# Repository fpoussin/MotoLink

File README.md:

View this project on [CADLAB.io](https://cadlab.io/node/808). 

MotoLink
===================

CAN Bus, K-Line interface for motorcycles, with a fuel/ignition mapper function.  

Primarily intended to communicate with Honda HRC, Generic OBD, or Yamaha YEC ECUs.  

This device will create a fuel map based on the various sensor inputs. You will then be able to alter the fuel using your prefered application. (HRC, TuneEcu, YEC, etc...)  
This replaces auto tune fuel systems like Bazzaz or Power commander, except you still have to enter the changes manually. (import/export functions are planned)  
Having a wideband exhaust sensor is mandatory. If your bike doesn't have one, you can use an innovate LC2.  

Includes some digital (RPM, Speed), analog (TPS, ECT, Wideband), serial (Wideband), as well as a knock sensor input interface for tuning.

### File tree:  
**├── Board**  *Eagle board files*  
**├── Code**  
**│   ├── App**  *Motolink's MCU code*  
**│   ├── Bootloader**  *STM32 Bootloader*  
**│   ├── ChibiOS-RT**  *ChibiOS/RT submodule*  
**│   ├── ChibiOS-Contrib**  *ChibiOS Community drivers submodule*  
**│   └── Common**  *Common files for bootloader and Motolink*  
**├── Drivers**  *Windows drivers installer*  
**├── GUI**  *Motolink's graphical user interface*  
**├── LICENSE**  *GPL Licence file*  
**└── README.md**  *This readme file*  

You will need to init and update the git submodules (QtUsb, ChibiOS-RT, ChibiOS-Contrib) to build the projects.

## Building
### GUI
* Make sure submodules are pulled
* You will need python 2/3 in the path (system path or Qt Creator project setting PATH variable)
* Go to the GUI folder
* Unzip res/oxygen.zip
* You need a binary file of the firmware, an empty one can be created for testing. (../code/app/build/motolink.bin)
* You need to install QtUsb (https://github.com/fpoussin/QtUsb)
* Open the project with Qt Creator
* Compile and launch

### App and Bootloader
* [You will need ARM's GCC toolchain](https://developer.arm.com/open-source/gnu-toolchain/gnu-rm/downloads)
* Make sure submodules are pulled
* Go the de code/app or code/bootloader folder
* For the app, you need to compile the DSP lib (just launch make in the dsp_lib folder)
* make
* For the bootloader, use your favorite stlink interface [or my QSTLink2 app](https://github.com/fpoussin/QStlink2)
* Once the bootloader is running, you can update the app through the GUI

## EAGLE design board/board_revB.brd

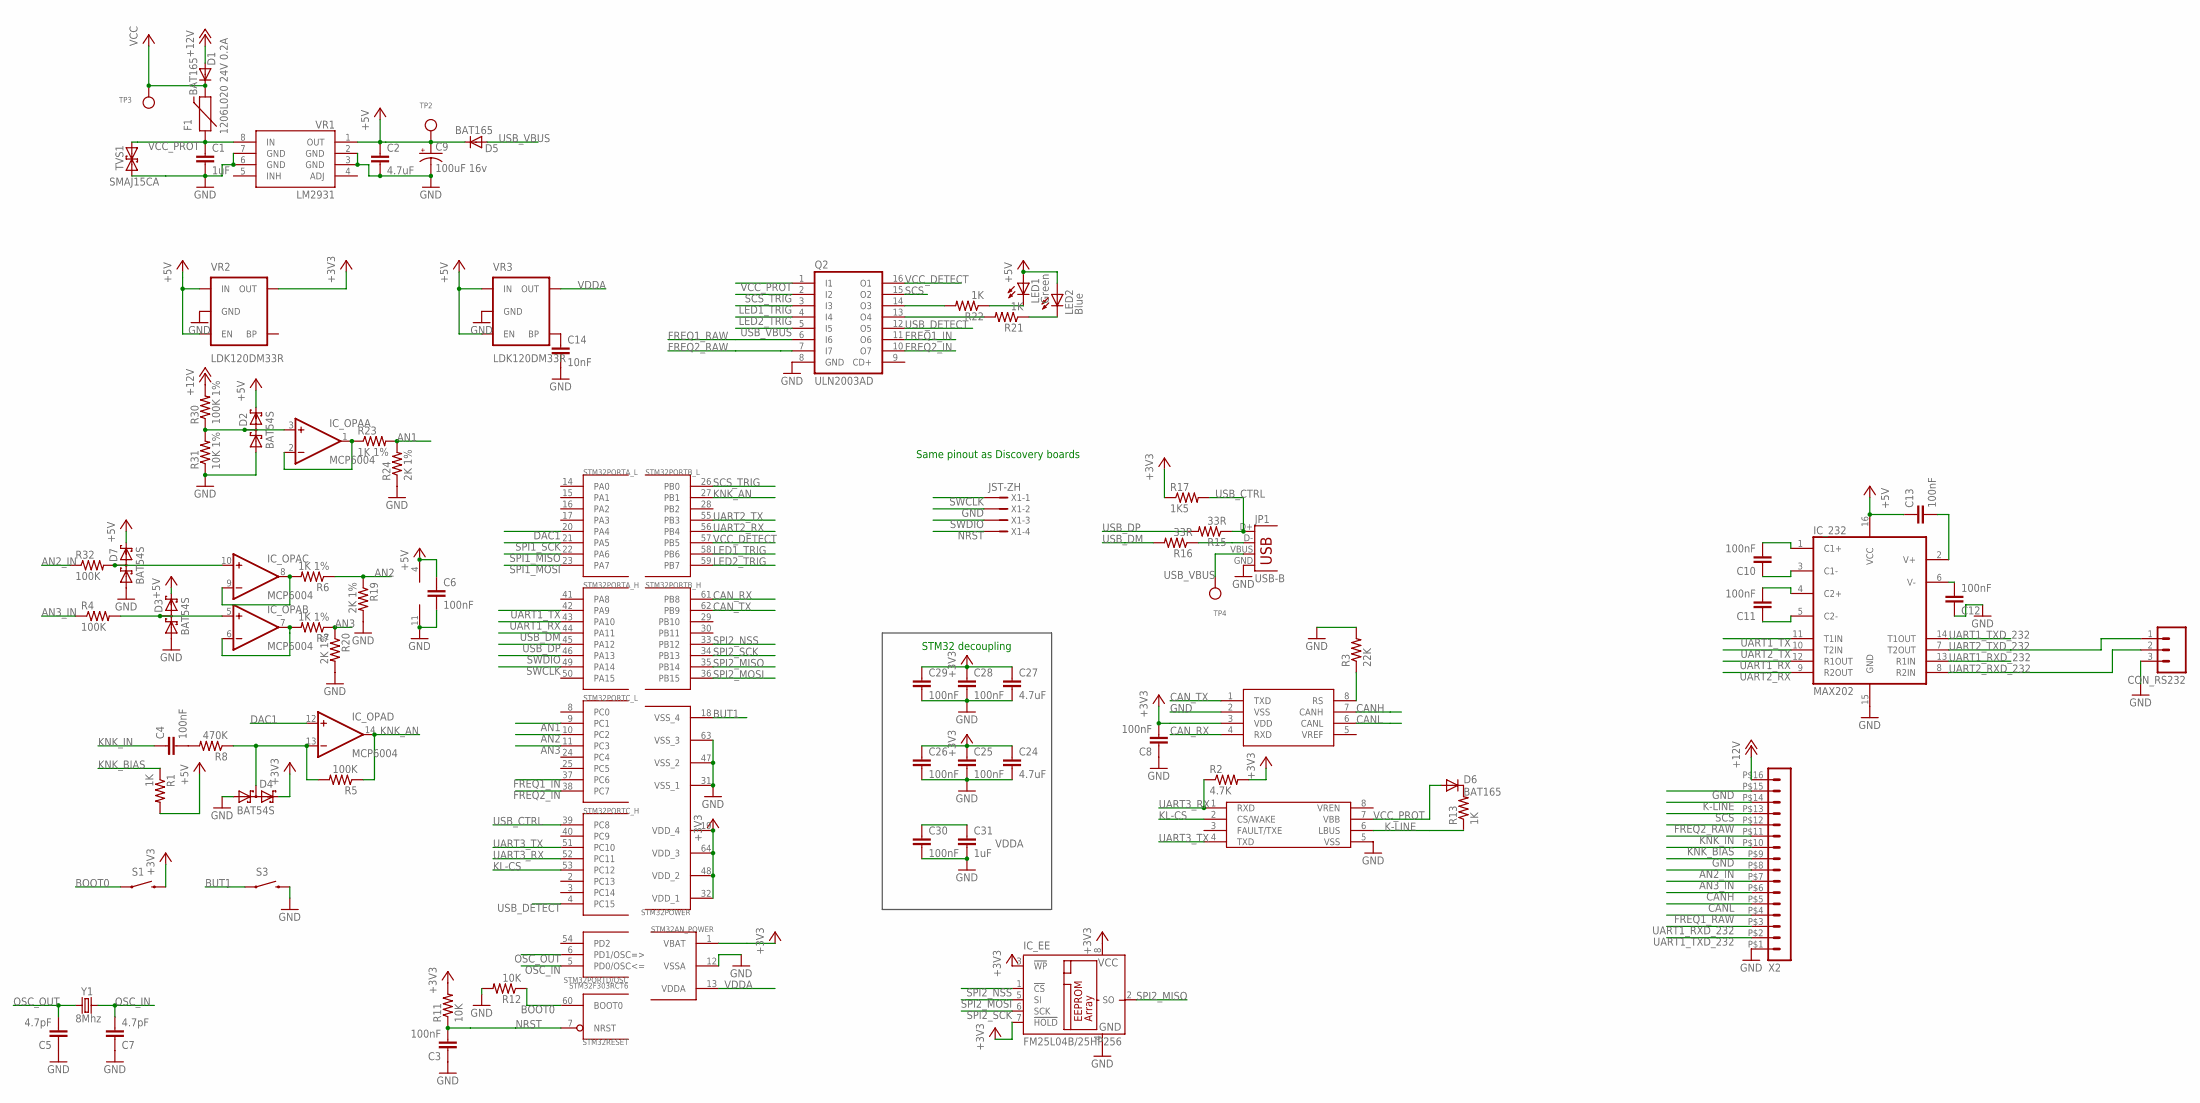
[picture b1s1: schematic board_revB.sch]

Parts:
C1, C31: 1uF; 0603-CAP
C2, C24, C27: 4.7uF; 0603-CAP
C3, C4, C6, C8, C10, C11, C12, C13, C25, C26, C28, C29, C30: 100nF; 0603-CAP
C5, C7: 4.7pF; 0603-CAP
C9: 100uF 16v; CPOL-RADIAL-10UF-25V
C14: 10nF; 0603-CAP
CON_RS232: M03LOCK; 1X03_LOCK
D1, D5, D6: BAT165; SOD-323
D2, D3, D4, D7: BAT54S; SOT23
F1: 1206L020 24V 0.2A; PTC-1206
IC_232: MAX202; TSSOP16
IC_CAN: MAX3051; SO08
IC_EE: FM25L04B/25HP256; SO-08
IC_KLINE: TJA1027; SO08
IC_OPA: MCP6004; TSSOP14
JP1: USB-B; USB-B-PTH
LED1: Green; LED3MM
LED2: Blue; LED3MM
Q2: ULN2003AD; SO16
R1, R13, R21, R22: 1K; 0603-RES
R2: 4.7K; 0603-RES
R3: 22K; 0603-RES
R4, R5, R32: 100K; 0603-RES
R6, R7, R23: 1K 1%; 0603-RES
R8: 470K; 0603-RES
R11, R12: 10K; 0603-RES
R15, R16: 33R; 0603-RES
R17: 1K5; 0603-RES
R19, R20, R24: 2K 1%; 0603-RES
R30: 100K 1%; 0603-RES
R31: 10K 1%; 0603-RES
S1: SWITCH-MOMENTARY-2SMD-4; TACTILE_SWITCH_TALL
S3: SWITCH-MOMENTARY-2SIDE_EZ; TACTILE-PTH-SIDEEZ
STM32: STM32F303RCT6; TQFP64
TP2, TP3, TP4: TESTPOINTROUND1MM; TESTPOINT_ROUND_1MM
TVS1: SMAJ15CA; SMA-DIODE
VR1: LM2931; SO08
VR2, VR3: LDK120DM33R; SOT23-5
X1: JST-ZH; S4B-ZR
X2: HEADER_POS16_43045-1600; 43045-1600
Y1: 8Mhz; HC49US

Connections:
+3V3: C8.2, C24.1, C25.1, C26.1, C27.1, C28.1, C29.1, D4.2 (C2), IC_CAN.3 (VDD), IC_EE.3 (!WP), IC_EE.7 (!HOLD), IC_EE.8 (VCC), R2.2, R11.2, R17.1, S1.B2 (2), STM32.1 (VBAT), STM32.19 (VDD_4), STM32.32 (VDD_1), STM32.48 (VDD_2), STM32.64 (VDD_3), VR2.5 (OUT)
+5V: C2.1, C6.1, C9.1 (+), C13.1, D2.2 (C2), D3.2 (C2), D5.1 (C), D7.2 (C2), IC_232.16 (VCC), IC_OPA.4 (V+), LED1.A, LED2.A, R1.2, TP2.P$1, VR1.1 (OUT), VR2.1 (IN), VR2.3 (EN), VR3.1 (IN), VR3.3 (EN)
+12V: D1.2 (A), R30.2, X2.P$16 (16)
AN1: R23.2, R24.2, STM32.9 (PC1)
AN1_N: IC_OPA.1 (OUT), IC_OPA.2 (-IN), R23.1
AN2: R6.1, R19.1, STM32.10 (PC2)
AN2_IN: R32.1, X2.P$8 (8)
AN2_N: IC_OPA.8 (OUT), IC_OPA.9 (-IN), R6.2
AN3: R7.1, R20.1, STM32.11 (PC3)
AN3_IN: R4.1, X2.P$7 (7)
AN3_N: IC_OPA.6 (-IN), IC_OPA.7 (OUT), R7.2
BOOT0: R12.1, S1.A2 (1), STM32.60 (BOOT0)
BUT1: S3.1, STM32.18 (VSS_4)
CANH: IC_CAN.7 (CANH), X2.P$6 (6)
CANL: IC_CAN.6 (CANL), X2.P$5 (5)
CAN_RX: IC_CAN.4 (RXD), STM32.61 (PB8)
CAN_TX: IC_CAN.1 (TXD), STM32.62 (PB9)
DAC1: IC_OPA.12 (+IN), STM32.20 (PA4)
FREQ1_IN: Q2.11 (O6), STM32.37 (PC6)
FREQ1_RAW: Q2.6 (I6), X2.P$4 (4)
FREQ2_IN: Q2.10 (O7), STM32.38 (PC7)
FREQ2_RAW: Q2.7 (I7), X2.P$12 (12)
GND: C1.2, C2.2, C3.1, C5.1, C6.2, C7.1, C8.1, C9.2 (-), C12.1, C14.2, C24.2, C25.2, C26.2, C27.2, C28.2, C29.2, C30.2, C31.2, CON_RS232.3, D2.1 (A1), D3.1 (A1), D4.1 (A1), D7.1 (A1), IC_232.15 (GND), IC_CAN.2 (VSS), IC_EE.4 (GND), IC_KLINE.5 (VSS), IC_OPA.11 (V-), JP1.GND, Q2.8 (GND), R3.2, R12.2, R19.2, R20.2, R24.1, R31.1, S3.2, STM32.12 (VSSA), STM32.31 (VSS_1), STM32.47 (VSS_2), STM32.63 (VSS_3), TVS1.A (1), VR1.2 (GND), VR1.3 (GND), VR1.6 (GND), VR1.7 (GND), VR2.2 (GND), VR3.2 (GND), X1.2, X2.P$1 (1), X2.P$9 (9), X2.P$15 (15)
K-LINE: IC_KLINE.6 (LBUS), R13.1, X2.P$14 (14)
KL-CS: IC_KLINE.2 (CS/WAKE), STM32.53 (PC12)
KNK_AN: IC_OPA.14 (OUT), R5.1, STM32.27 (PB1)
KNK_BIAS: R1.1, X2.P$10 (10)
KNK_IN: C4.1, X2.P$11 (11)
LED1_TRIG: Q2.3 (I3), STM32.58 (PB6)
LED2_TRIG: Q2.4 (I4), STM32.59 (PB7)
unnamed: D4.3 (C1A2), IC_OPA.13 (-IN), R5.2, R8.1
unnamed: D3.3 (C1A2), IC_OPA.5 (+IN), R4.2
unnamed: C4.2, R8.2
unnamed: IC_CAN.8 (RS), R3.1
unnamed: C14.1, VR3.4 (BP)
unnamed: LED2.K (C), R21.1
unnamed: Q2.13 (O4), R21.2
unnamed: D6.1 (C), R13.2
unnamed: Q2.14 (O3), R22.2
unnamed: JP1.D-, R16.1
unnamed: LED1.K (C), R22.1
unnamed: C11.2, IC_232.4 (C2+)
unnamed: C11.1, IC_232.5 (C2-)
unnamed: C10.1, IC_232.3 (C1-)
unnamed: D2.3 (C1A2), IC_OPA.3 (+IN), R30.1, R31.2
unnamed: D7.3 (C1A2), IC_OPA.10 (+IN), R32.2
unnamed: C10.2, IC_232.1 (C1+)
unnamed: C12.2, IC_232.6 (V-)
unnamed: C13.2, IC_232.2 (V+)
NRST: C3.2, R11.1, STM32.7 (NRST), X1.4
OSC_IN: C7.2, STM32.5 (PD0/OSC<=), Y1.2
OSC_OUT: C5.2, STM32.6 (PD1/OSC=>), Y1.1
SCS: Q2.15 (O2), X2.P$13 (13)
SCS_TRIG: Q2.2 (I2), STM32.26 (PB0)
SPI1_MISO: STM32.22 (PA6)
SPI1_MOSI: STM32.23 (PA7)
SPI1_SCK: STM32.21 (PA5)
SPI2_MISO: IC_EE.2 (SO), STM32.35 (PB14)
SPI2_MOSI: IC_EE.5 (SI), STM32.36 (PB15)
SPI2_NSS: IC_EE.1 (!CS), STM32.33 (PB12)
SPI2_SCK: IC_EE.6 (SCK), STM32.34 (PB13)
SWCLK: STM32.49 (PA14), X1.1
SWDIO: STM32.46 (PA13), X1.3
UART1_RX: IC_232.12 (R1OUT), STM32.43 (PA10)
UART1_RXD_232: IC_232.13 (R1IN), X2.P$3 (3)
UART1_TX: IC_232.11 (T1IN), STM32.42 (PA9)
UART1_TXD_232: IC_232.14 (T1OUT), X2.P$2 (2)
UART2_RX: IC_232.9 (R2OUT), STM32.56 (PB4)
UART2_RXD_232: CON_RS232.2, IC_232.8 (R2IN)
UART2_TX: IC_232.10 (T2IN), STM32.55 (PB3)
UART2_TXD_232: CON_RS232.1, IC_232.7 (T2OUT)
UART3_RX: IC_KLINE.1 (RXD), R2.1, STM32.52 (PC11)
UART3_TX: IC_KLINE.4 (TXD), STM32.51 (PC10)
USB_CTRL: JP1.D+, R15.1, R17.2, STM32.39 (PC8)
USB_DETECT: Q2.12 (O5), STM32.4 (PC15)
USB_DM: R16.2, STM32.44 (PA11)
USB_DP: R15.2, STM32.45 (PA12)
USB_VBUS: D5.2 (A), JP1.VBUS, Q2.5 (I5), TP4.P$1
VCC: D1.1 (C), F1.2, TP3.P$1
VCC_DETECT: Q2.16 (O1), STM32.57 (PB5)
VCC_PROT: C1.1, D6.2 (A), F1.1, IC_KLINE.7 (VBB), Q2.1 (I1), TVS1.C (2), VR1.8 (IN)
VDDA: C30.1, C31.1, STM32.13 (VDDA), VR3.5 (OUT)

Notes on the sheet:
STM32 decoupling
Same pinout as Discovery boards

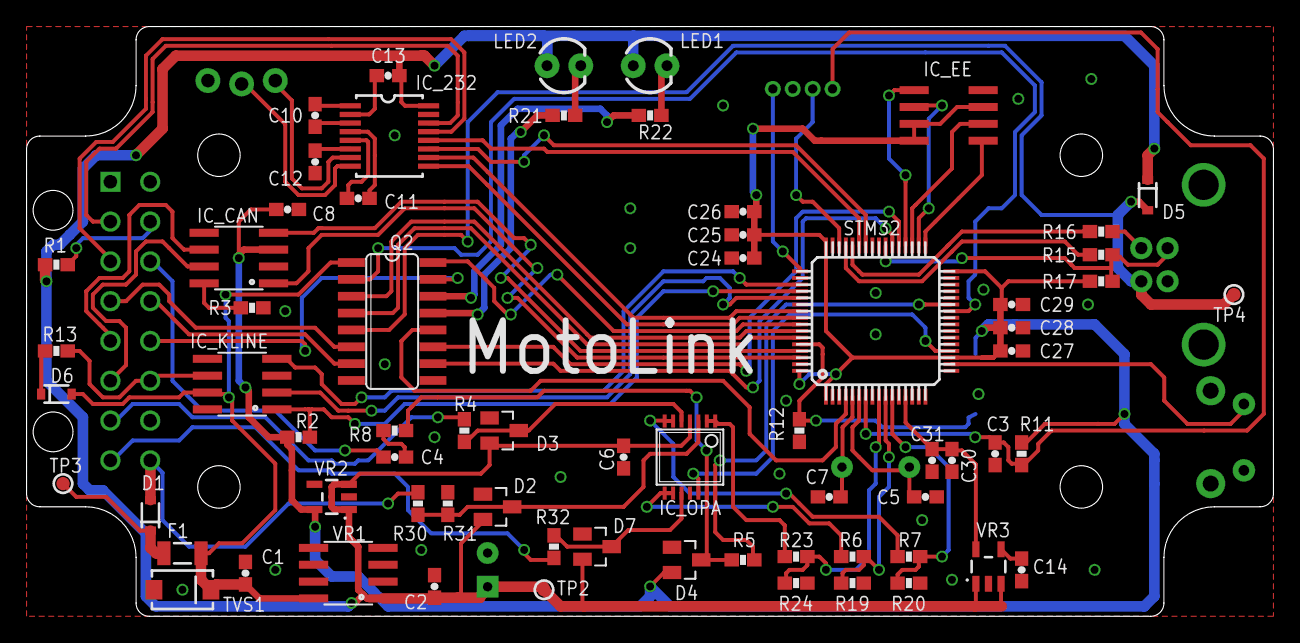
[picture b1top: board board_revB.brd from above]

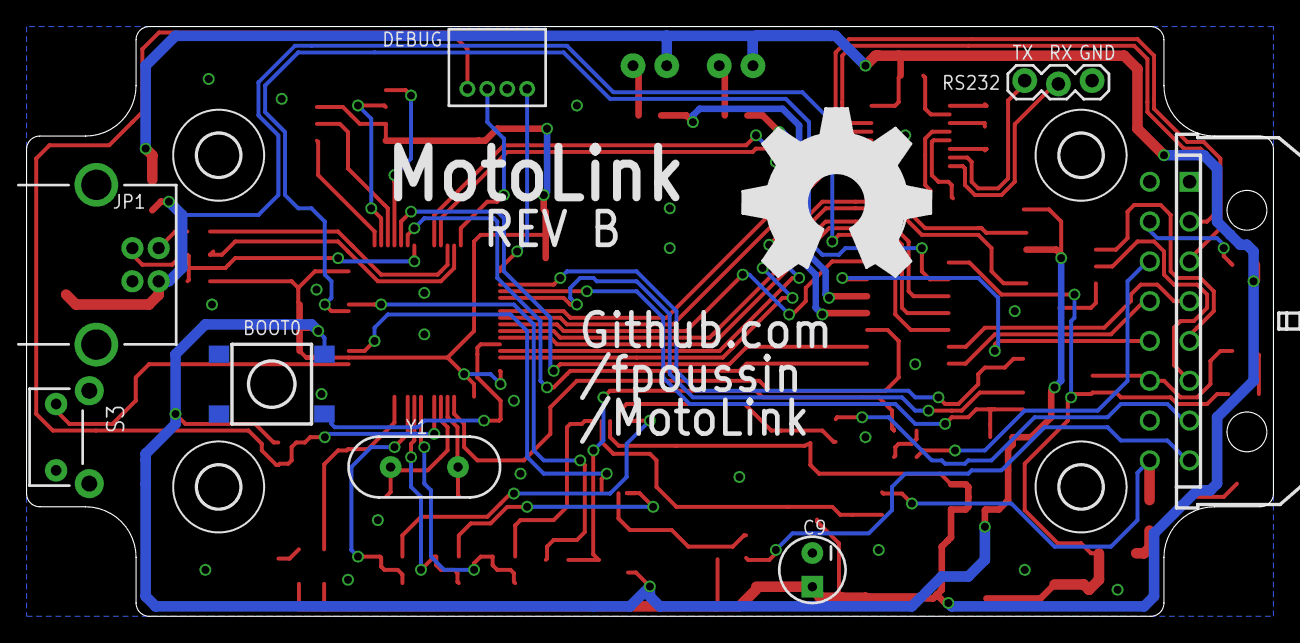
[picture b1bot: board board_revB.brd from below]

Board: 2 copper layers, 94.0 x 44.5 mm, 81 parts (13 on the bottom side), 79 nets.

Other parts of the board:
U$2, U$3, U$4, U$5: 3,2
U$6: OSHW_FILLX500_NOTEXT

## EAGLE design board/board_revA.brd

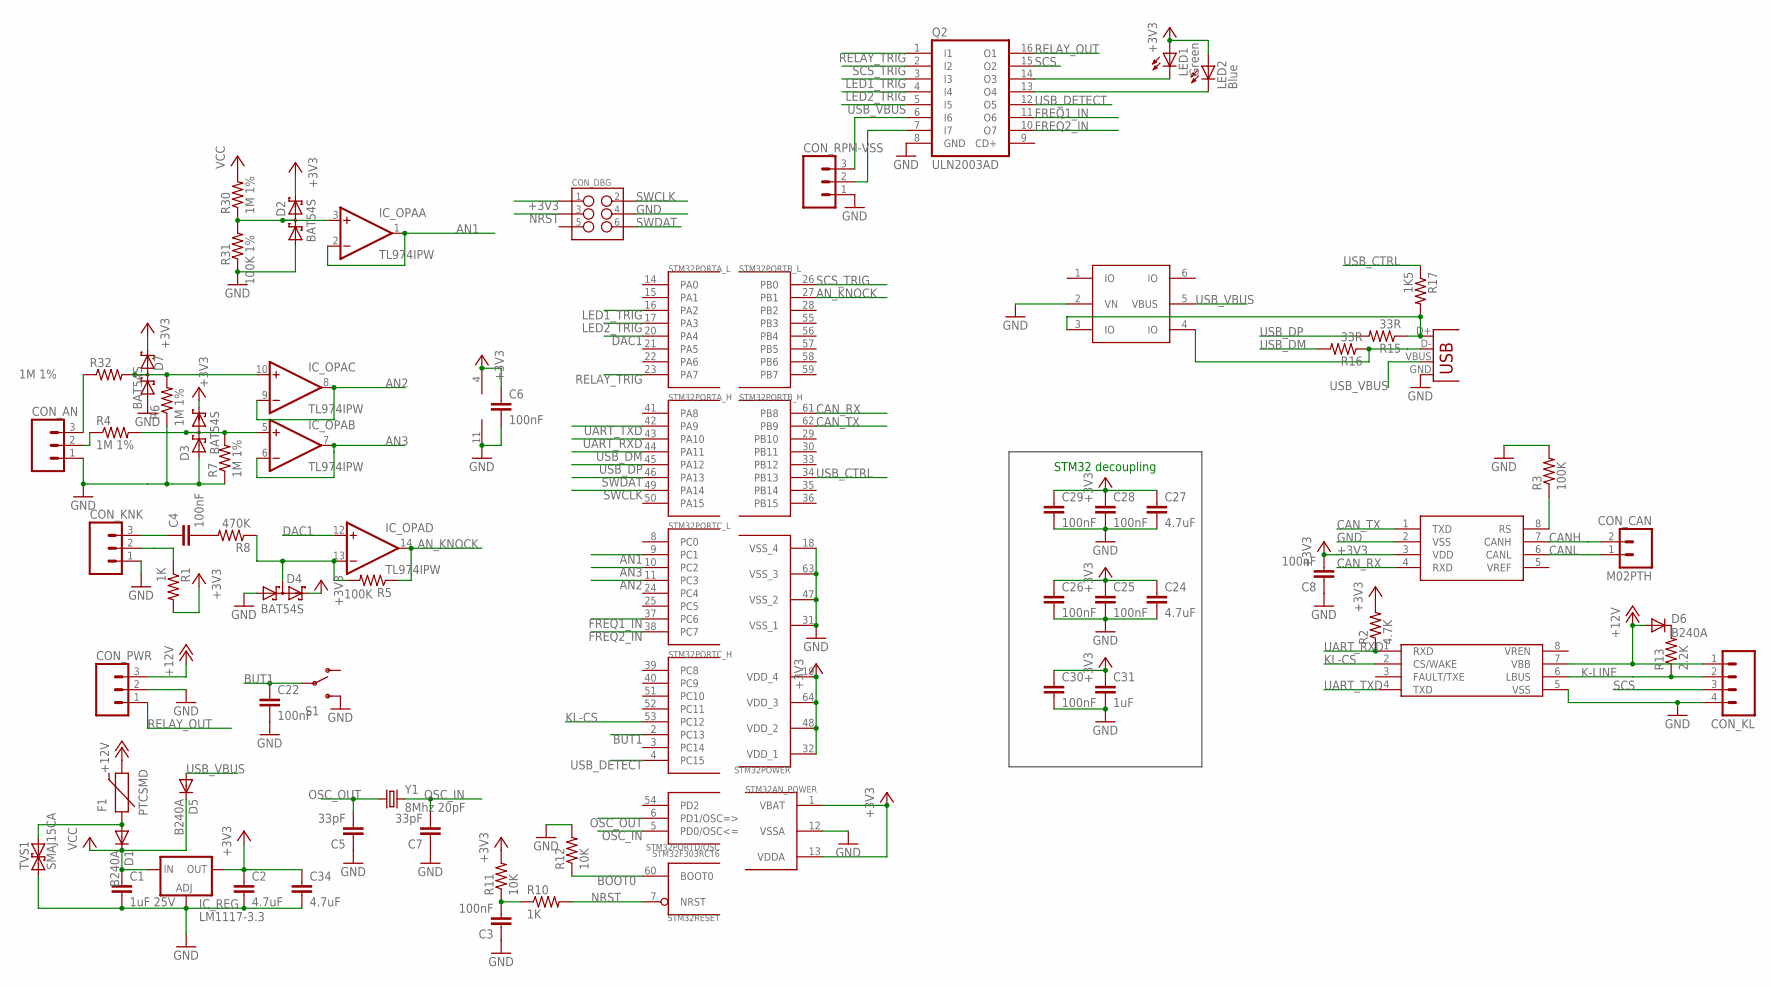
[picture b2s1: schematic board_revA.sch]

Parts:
C1: 1uF 25V; 0603-CAP
C2, C24, C27, C34: 4.7uF; 0603-CAP
C3, C4, C6, C8, C22, C25, C26, C28, C29, C30: 100nF; 0603-CAP
C5, C7: 33pF; 0603-CAP
C31: 1uF; 0603-CAP
CON_AN: M03PTH; 1X03
CON_CAN: M02PTH; 1X02
CON_DBG: M03X22X3_SILK_SM; 2X3
CON_KL: M04PTH; 1X04
CON_KNK: M03PTH; 1X03
CON_PWR: M03PTH; 1X03
CON_RPM-VSS: M03PTH; 1X03
CON_USB: USBSMD; USB-MINIB
D1, D5, D6: B240A; SMA-DIODE
D2, D3, D4, D7: BAT54S; SOT23
F1: PTCSMD; PTC-1206
IC_CAN: MAX3051; SO08
IC_KLINE: MCP2004; SO08
IC_OPA: TL974IPW; TSSOP14
IC_REG: LM1117-3.3; DPACK
LED1: Green; LED3MM
LED2: Blue; LED3MM
Q2: ULN2003AD; SO16
R1, R10: 1K; 0603-RES
R2: 4.7K; 0603-RES
R3, R5: 100K; 0603-RES
R4, R6, R7, R30, R32: 1M 1%; 0603-RES
R8: 470K; 0603-RES
R11, R12: 10K; 0603-RES
R13: 2.2K; 0603-RES
R15, R16: 33R; 0603-RES
R17: 1K5; 0603-RES
R31: 100K 1%; 0603-RES
S1: SWITCH-SPDTPTH; SWITCH-SPDT
STM32: STM32F303RCT6; TQFP64
TVS1: SMAJ15CA; SMA-DIODE
TVS2: NUP4201MR6; SOT23-6
Y1: 8Mhz 20pF; HC49US

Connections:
+3V3: C2.1, C6.1, C8.2, C24.1, C25.1, C26.1, C27.1, C28.1, C29.1, C30.1, C31.1, C34.1, CON_DBG.1, D2.2 (C2), D3.2 (C2), D4.2 (C2), D7.2 (C2), IC_CAN.3 (VDD), IC_OPA.4 (V+), IC_REG.4 (OUT), LED1.A, LED2.A, R1.2, R2.2, R11.2, STM32.1 (VBAT), STM32.13 (VDDA), STM32.19 (VDD_4), STM32.32 (VDD_1), STM32.48 (VDD_2), STM32.64 (VDD_3)
+12V: CON_KL.1, CON_PWR.3, D6.A, F1.2, IC_KLINE.7 (VBB)
AN1: IC_OPA.1 (OUT), IC_OPA.2 (-IN), STM32.9 (PC1)
AN2: IC_OPA.8 (OUT), IC_OPA.9 (-IN), STM32.11 (PC3)
AN3: IC_OPA.6 (-IN), IC_OPA.7 (OUT), STM32.10 (PC2)
AN_KNOCK: IC_OPA.14 (OUT), R5.1, STM32.27 (PB1)
BOOT0: R12.1, STM32.60 (BOOT0)
BUT1: C22.1, S1.2, STM32.2 (PC13)
CANH: CON_CAN.2, IC_CAN.7 (CANH)
CANL: CON_CAN.1, IC_CAN.6 (CANL)
CAN_RX: IC_CAN.4 (RXD), STM32.61 (PB8)
CAN_TX: IC_CAN.1 (TXD), STM32.62 (PB9)
DAC1: IC_OPA.12 (+IN), STM32.20 (PA4)
FREQ1_IN: Q2.11 (O6), STM32.37 (PC6)
FREQ2_IN: Q2.10 (O7), STM32.38 (PC7)
GND: C1.2, C2.2, C3.1, C5.1, C6.2, C7.1, C8.1, C22.2, C24.2, C25.2, C26.2, C27.2, C28.2, C29.2, C30.2, C31.2, C34.2, CON_AN.1, CON_DBG.4, CON_KL.4, CON_KNK.1, CON_PWR.2, CON_RPM-VSS.1, CON_USB.GND, D2.1 (A1), D3.1 (A1), D4.1 (A1), D7.1 (A1), IC_CAN.2 (VSS), IC_KLINE.5 (VSS), IC_OPA.11 (V-), IC_REG.1 (ADJ), Q2.8 (GND), R3.2, R6.1, R7.1, R12.2, R31.1, S1.3 (S), STM32.12 (VSSA), STM32.18 (VSS_4), STM32.31 (VSS_1), STM32.47 (VSS_2), STM32.63 (VSS_3), TVS1.A (1), TVS2.2 (VN)
K-LINE: CON_KL.2, IC_KLINE.6 (LBUS), R13.1
KL-CS: IC_KLINE.2 (CS/WAKE), STM32.53 (PC12)
LED1_TRIG: Q2.3 (I3), STM32.16 (PA2)
LED2_TRIG: Q2.4 (I4), STM32.17 (PA3)
unnamed: CON_KNK.2, R1.1
unnamed: CON_AN.3, R32.1
unnamed: CON_AN.2, R4.1
unnamed: C4.1, CON_KNK.3
unnamed: D3.3 (C1A2), IC_OPA.5 (+IN), R4.2, R7.2
unnamed: C4.2, R8.2
unnamed: CON_USB.D+, R15.1, R17.2, TVS2.3 (IO)
unnamed: IC_CAN.8 (RS), R3.1
unnamed: D1.A, F1.1, TVS1.C (2)
unnamed: LED1.K (C), Q2.14 (O3)
unnamed: LED2.K (C), Q2.13 (O4)
unnamed: D4.3 (C1A2), IC_OPA.13 (-IN), R5.2, R8.1
unnamed: D6.C, R13.2
unnamed: CON_RPM-VSS.3, Q2.6 (I6)
unnamed: CON_USB.D-, R16.1, TVS2.4 (IO)
unnamed: C3.2, R10.1, R11.1
unnamed: CON_RPM-VSS.2, Q2.7 (I7)
unnamed: D2.3 (C1A2), IC_OPA.3 (+IN), R30.1, R31.2
unnamed: D7.3 (C1A2), IC_OPA.10 (+IN), R6.2, R32.2
NRST: CON_DBG.3, R10.2, STM32.7 (NRST)
OSC_IN: C7.2, STM32.5 (PD0/OSC<=), Y1.2
OSC_OUT: C5.2, STM32.6 (PD1/OSC=>), Y1.1
RELAY_OUT: CON_PWR.1, Q2.16 (O1)
RELAY_TRIG: Q2.1 (I1), STM32.23 (PA7)
SCS: CON_KL.3, Q2.15 (O2)
SCS_TRIG: Q2.2 (I2), STM32.26 (PB0)
SWCLK: CON_DBG.2, STM32.49 (PA14)
SWDAT: CON_DBG.6, STM32.46 (PA13)
UART_RXD: IC_KLINE.1 (RXD), R2.1, STM32.43 (PA10)
UART_TXD: IC_KLINE.4 (TXD), STM32.42 (PA9)
USB_CTRL: R17.1, STM32.34 (PB13)
USB_DETECT: Q2.12 (O5), STM32.4 (PC15)
USB_DM: R16.2, STM32.44 (PA11)
USB_DP: R15.2, STM32.45 (PA12)
USB_VBUS: CON_USB.VBUS, D5.A, Q2.5 (I5), TVS2.5 (VBUS)
VCC: C1.1, D1.C, D5.C, IC_REG.3 (IN), R30.2

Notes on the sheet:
STM32 decoupling

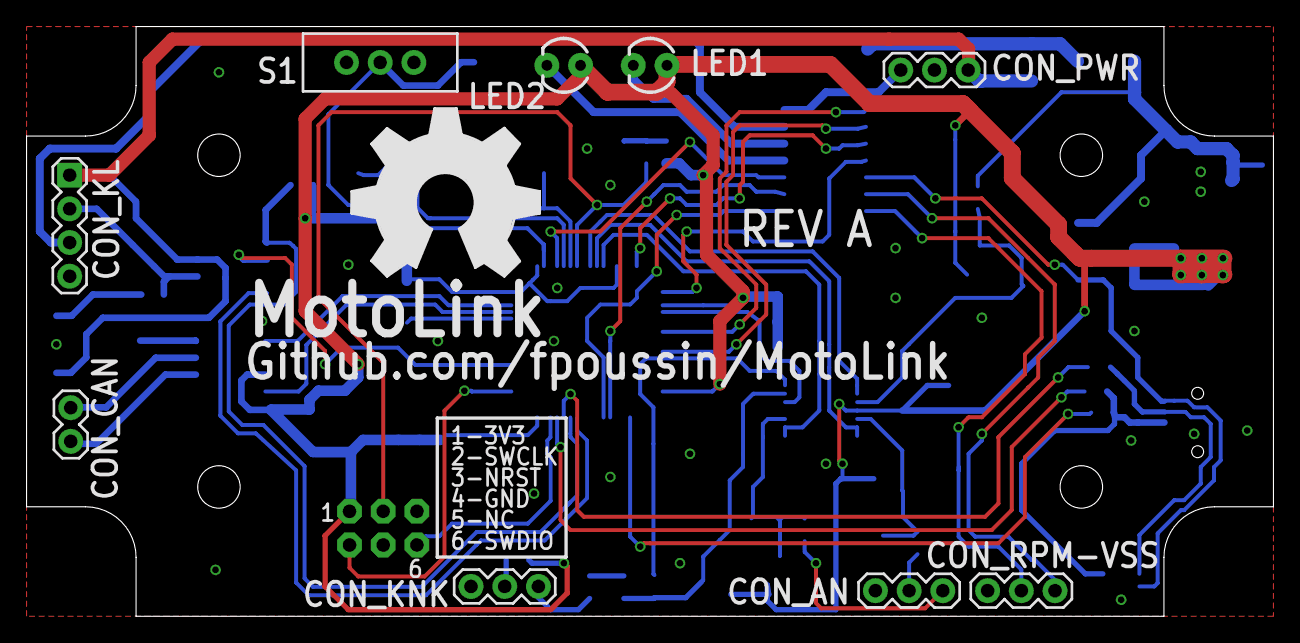
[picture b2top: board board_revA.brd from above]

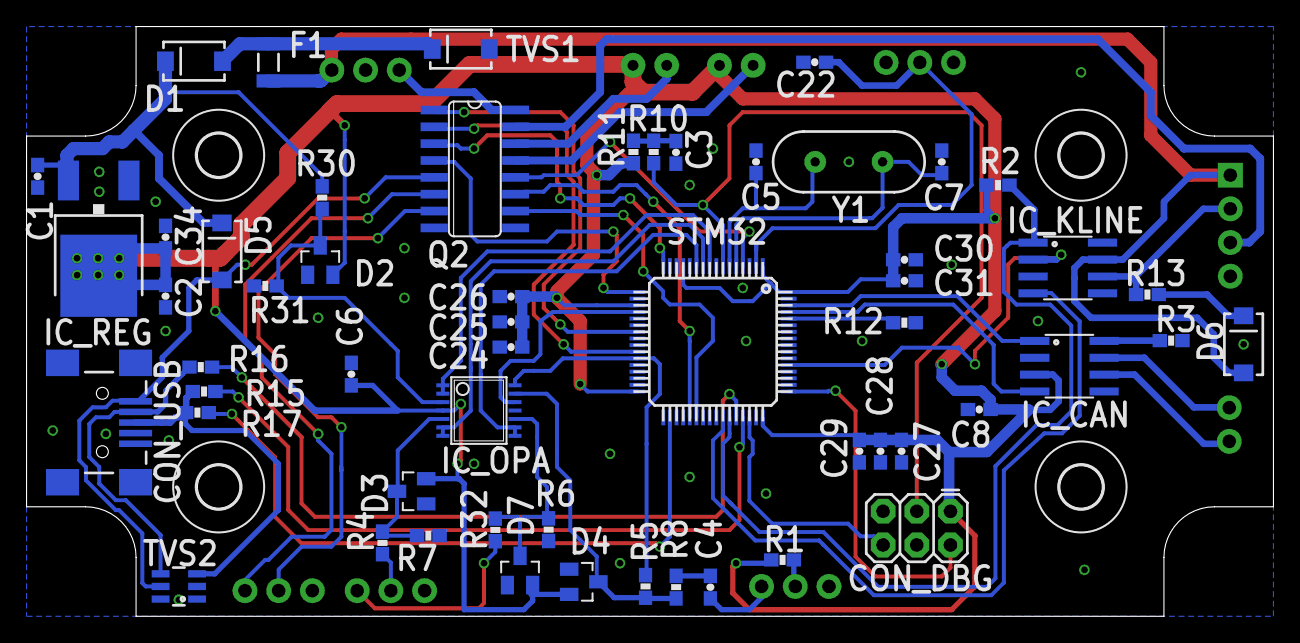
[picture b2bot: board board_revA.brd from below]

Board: 2 copper layers, 94.0 x 44.5 mm, 69 parts (59 on the bottom side), 56 nets.

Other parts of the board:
U$2, U$3, U$4, U$5: 3,2
U$6: OSHW_FILLX500_NOTEXT

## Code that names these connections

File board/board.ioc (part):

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Mcu.Name=STM32F303R(B-C)Tx
Mcu.Package=LQFP64
Mcu.UserName=STM32F303R(B-C)Tx
PA10.GPIOParameters=GPIO_Speed,GPIO_PuPd,GPIO_OType,GPIO_Mode
PA10.GPIO_Mode=GPIO_MODE_AF_PP
PA10.GPIO_OType=N/A
PA10.GPIO_PuPd=GPIO_PULLUP
PA10.GPIO_Speed=GPIO_SPEED_FREQ_MEDIUM
PA10.Mode=Asynchronous
PA10.Signal=USART1_RX
PA11.Mode=Device
PA11.Signal=USB_DM
PA12.Mode=Device
PA12.Signal=USB_DP
PA13.Mode=Serial_Wire
PA13.Signal=SYS_JTMS-SWDIO
PA14.Mode=Serial_Wire
PA14.Signal=SYS_JTCK-SWCLK
PA4.GPIOParameters=GPIO_PuPd,GPIO_Label,GPIO_Mode
PA4.GPIO_Label=KNOCK_OFFSET
PA4.GPIO_Mode=GPIO_MODE_ANALOG
PA4.GPIO_PuPd=GPIO_NOPULL
PA4.Signal=COMP_DAC1_group
PA9.GPIOParameters=GPIO_Speed,GPIO_PuPd,GPIO_OType,GPIO_Mode
PA9.GPIO_Mode=GPIO_MODE_AF_PP
PA9.GPIO_OType=N/A
PA9.GPIO_PuPd=GPIO_PULLUP
PA9.GPIO_Speed=GPIO_SPEED_FREQ_MEDIUM
PA9.Mode=Asynchronous
PA9.Signal=USART1_TX
PB0.GPIOParameters=GPIO_Speed,GPIO_PuPd,GPIO_Label,GPIO_ModeDefaultOutputPP
PB0.GPIO_Label=SCS_TRIG
PB0.GPIO_ModeDefaultOutputPP=GPIO_MODE_OUTPUT_PP
PB0.GPIO_PuPd=GPIO_NOPULL
PB0.GPIO_Speed=GPIO_SPEED_FREQ_LOW
PB0.Signal=GPIO_Output
PB1.GPIOParameters=GPIO_PuPd,GPIO_Label,GPIO_Mode
PB1.GPIO_Label=KNK_AN
PB1.GPIO_Mode=GPIO_MODE_ANALOG
PB1.GPIO_PuPd=GPIO_NOPULL
PB1.Mode=IN1-Single-Ended
PB1.Signal=ADC3_IN1
PB12.Mode=NSS_Signal_Hard_Input
PB12.Signal=SPI2_NSS
PB13.Mode=Full_Duplex_Master
PB13.Signal=SPI2_SCK
PB14.Mode=Full_Duplex_Master
PB14.Signal=SPI2_MISO
PB15.Mode=Full_Duplex_Master
PB15.Signal=SPI2_MOSI
PB3.GPIOParameters=GPIO_Speed
PB3.GPIO_Speed=GPIO_SPEED_FREQ_MEDIUM
PB3.Mode=Asynchronous
PB3.Signal=USART2_TX
PB4.GPIOParameters=GPIO_Speed
PB4.GPIO_Speed=GPIO_SPEED_FREQ_MEDIUM
PB4.Mode=Asynchronous
PB4.Signal=USART2_RX
PB5.GPIOParameters=GPIO_PuPd,GPIO_Label
PB5.GPIO_Label=VCC_DETECT
PB5.GPIO_PuPd=GPIO_PULLUP
PB5.Signal=GPIO_Input
PB6.GPIOParameters=GPIO_ModeDefaultPP,GPIO_Speed,GPIO_FM6,GPIO_PuPd,GPIO_Label
PB6.GPIO_FM6=__NULL
PB6.GPIO_Label=LED1
PB6.GPIO_ModeDefaultPP=GPIO_MODE_AF_PP
PB6.GPIO_PuPd=GPIO_NOPULL
PB6.GPIO_Speed=GPIO_SPEED_FREQ_LOW
PB6.Signal=S_TIM4_CH1
PB7.GPIOParameters=GPIO_ModeDefaultPP,GPIO_Speed,GPIO_PuPd,GPIO_Label,GPIO_FM7
PB7.GPIO_FM7=__NULL
PB7.GPIO_Label=LED2
PB7.GPIO_ModeDefaultPP=GPIO_MODE_AF_PP
PB7.GPIO_PuPd=GPIO_NOPULL
PB7.GPIO_Speed=GPIO_SPEED_FREQ_LOW
PB7.Signal=S_TIM4_CH2
PB8.GPIOParameters=GPIO_Speed,GPIO_PuPd,GPIO_FM8,GPIO_Mode
PB8.GPIO_FM8=__NULL
PB8.GPIO_Mode=GPIO_MODE_AF_PP
PB8.GPIO_PuPd=GPIO_NOPULL
PB8.GPIO_Speed=GPIO_SPEED_FREQ_MEDIUM
PB8.Mode=Master
PB8.Signal=CAN_RX
PB9.GPIOParameters=GPIO_Speed,GPIO_PuPd,GPIO_Mode,GPIO_FM9
PB9.GPIO_FM9=__NULL
PB9.GPIO_Mode=GPIO_MODE_AF_PP
PB9.GPIO_PuPd=GPIO_NOPULL
PB9.GPIO_Speed=GPIO_SPEED_FREQ_MEDIUM
PB9.Mode=Master
PB9.Signal=CAN_TX
PC1.GPIOParameters=GPIO_PuPd,GPIO_Label,GPIO_Mode
PC1.GPIO_Label=AN0
PC1.GPIO_Mode=GPIO_MODE_ANALOG
PC1.GPIO_PuPd=GPIO_NOPULL
PC1.Signal=ADCx_IN7
PC10.GPIOParameters=GPIO_Speed,GPIO_Label
PC10.GPIO_Label=KLINE-TX
PC10.GPIO_Speed=GPIO_SPEED_FREQ_MEDIUM
PC10.Mode=Asynchronous
PC10.Signal=USART3_TX
PC11.GPIOParameters=GPIO_Speed,GPIO_Label
PC11.GPIO_Label=KLINE-RX
PC11.GPIO_Speed=GPIO_SPEED_FREQ_MEDIUM
PC11.Mode=Asynchronous
PC11.Signal=USART3_RX
PC12.GPIOParameters=GPIO_Speed,GPIO_PuPd,GPIO_Label,GPIO_ModeDefaultOutputPP
PC12.GPIO_Label=KLINE-CS
PC12.GPIO_ModeDefaultOutputPP=GPIO_MODE_OUTPUT_PP
PC12.GPIO_PuPd=GPIO_NOPULL
PC12.GPIO_Speed=GPIO_SPEED_FREQ_LOW
PC12.Signal=GPIO_Output
PC15-OSC32_OUT.GPIOParameters=GPIO_PuPd,GPIO_Label,GPIO_Mode
PC15-OSC32_OUT.GPIO_Label=USB_DETECT
PC15-OSC32_OUT.GPIO_Mode=GPIO_MODE_INPUT
PC15-OSC32_OUT.GPIO_PuPd=GPIO_PULLUP
PC15-OSC32_OUT.Signal=GPIO_Input
PC2.GPIOParameters=GPIO_PuPd,GPIO_Label,GPIO_Mode
PC2.GPIO_Label=AN1
PC2.GPIO_Mode=GPIO_MODE_ANALOG
PC2.GPIO_PuPd=GPIO_NOPULL
PC2.Signal=ADCx_IN8
PC3.GPIOParameters=GPIO_PuPd,GPIO_Label,GPIO_Mode
PC3.GPIO_Label=AN2
PC3.GPIO_Mode=GPIO_MODE_ANALOG
PC3.GPIO_PuPd=GPIO_NOPULL
PC3.Signal=ADCx_IN9
PC6.GPIOParameters=GPIO_PuPd,GPIO_Label
PC6.GPIO_Label=FREQ2_IN
PC6.GPIO_PuPd=GPIO_PULLUP
PC6.Signal=S_TIM3_CH1
PC7.GPIOParameters=GPIO_PuPd,GPIO_Label
PC7.GPIO_Label=FREQ1_IN
PC7.GPIO_PuPd=GPIO_PULLUP
PC7.Signal=S_TIM3_CH2
PC8.GPIOParameters=GPIO_Speed,GPIO_PuPd,GPIO_Label,GPIO_ModeDefaultOutputPP
PC8.GPIO_Label=USB_CTRL
PC8.GPIO_ModeDefaultOutputPP=GPIO_MODE_OUTPUT_OD
PC8.GPIO_PuPd=GPIO_NOPULL
PC8.GPIO_Speed=GPIO_SPEED_FREQ_LOW
PC8.Signal=GPIO_Output
PF0-OSC_IN.Mode=HSE-External-Oscillator
PF0-OSC_IN.Signal=RCC_OSC_IN
PF1-OSC_OUT.Mode=HSE-External-Oscillator
PF1-OSC_OUT.Signal=RCC_OSC_OUT
PF4.GPIOParameters=GPIO_PuPd,GPIO_Label,GPIO_Mode
PF4.GPIO_Label=BUTTON1
PF4.GPIO_Mode=GPIO_MODE_INPUT
PF4.GPIO_PuPd=GPIO_PULLUP
PF4.Signal=GPIO_Input
RCC.HSEPLLFreq_Value=8000000
RCC.HSE_VALUE=8000000
RCC.SYSCLKFreq_VALUE=72000000
RCC.SYSCLKSourceVirtual=RCC_SYSCLKSOURCE_PLLCLK

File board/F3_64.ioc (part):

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Mcu.Name=STM32F303R(B-C)Tx
Mcu.Package=LQFP64
Mcu.UserName=STM32F303R(B-C)Tx
PA10.Mode=Asynchronous
PA10.Signal=USART1_RX
PA11.Mode=Dummy
PA11.Signal=USB_DM
PA12.Mode=Dummy
PA12.Signal=USB_DP
PA13.Mode=Serial-Wire
PA13.Signal=SYS_JTMS-SWDIO
PA14.Mode=Serial-Wire
PA14.Signal=SYS_JTCK-SWCLK
PA2.Signal=TIM2_CH3
PA3.Signal=TIM2_CH4
PA4.Mode=OUT1
PA4.Signal=DAC_OUT1
PA7.Signal=GPIO_Output
PA9.Mode=Asynchronous
PA9.Signal=USART1_TX
PB0.Signal=GPIO_Output
PB1.Mode=CH1-Single-Ended
PB1.Signal=ADC3_IN1
PB13.Signal=GPIO_Output
PB6.Signal=GPIO_Output
PB8.Mode=Master
PB8.Signal=CAN_RX
PB9.Mode=Master
PB9.Signal=CAN_TX
PC1.Mode=CH7-Single-Ended
PC1.Signal=ADC1_IN7
PC12.Signal=GPIO_Output
PC13.Signal=GPIO_Input
PC15-OSC32_OUT.Signal=GPIO_Input
PC2.Mode=CH8-Single-Ended
PC2.Signal=ADC1_IN8
PC3.Mode=CH9-Single-Ended
PC3.Signal=ADC1_IN9
PC6.Mode=Encoder-Interface
PC6.Signal=TIM3_CH1
PC7.Mode=Encoder-Interface
PC7.Signal=TIM3_CH2
PF0-OSC_IN.Mode=HSE-External-Oscillator
PF0-OSC_IN.Signal=SYS_OSC_IN
PF1-OSC_OUT.Mode=HSE-External-Oscillator
PF1-OSC_OUT.Signal=SYS_OSC_OUT

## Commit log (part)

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2014-05-04 [GUI] Adding language flags, updated translation
2014-05-04 [GUI] Working on tables.
2014-05-05 [Board Rev B] Moving the decoupling caps closer
2014-05-06 [GUI] Adding background color functions for tables.
2014-05-06 [GUI] Working on Undo/Redo.
2014-05-06 [GUI] Adding more details to Undo actions
2014-05-06 [GUI] Adding undo/redo menu auto enable
2014-05-06 [GUI] Tweaking colors, updated translation
2014-05-06 [GUI] Adding some code to support context menus
2014-05-07 [GUI] Fixed GCC compile error.
2014-05-07 [GUI] Working on shortcuts and undo.
2014-05-07 [GUI] Working on Undo for spinboxes.
2014-05-09 [GUI] Fixed Undo for spinboxes
2014-05-12 [Board Rev A] Tweaking resistor values
2014-05-23 [Board Rev A] Tweaking capacitor values
2014-05-28 [GUI/Code] Working on bootloader integration.
2014-05-28 [GUI] Updated QtUsb
2014-05-30 [Code/GUI] Working on bootloader improvements. Merging/sharing some code with main app.
2014-05-31 [GUI/Code] Still working on bootloader improvements. Merging more code.
2014-06-01 [GUI/Code] Still working on bootloader improvements.
2014-06-03 [GUI/Code] More work on bootloader. Now boots fine.
2014-06-04 [Code] Working on communication.h
2014-06-05 [GUI] Update wizard improvements. Adding script for FW file generation.
2014-06-05 [GUI] Adding release version check using GitHub's API.
2014-06-08 [Gui/Code] Still working on ADC stuff.
2014-06-09 [GUI] Changed help system [Code] Adding frequency measurement.
2014-06-09 [Code] Working on timer bugs.
2014-06-11 [GUI/Code] debugging USB crashes
2014-06-12 [GUI] Working on graphs
2014-06-13 [Code] Changed serial to half-duplex for K-Line.
2014-06-13 [Code] Adding DAC.
2014-06-15 [Code] Crashes are fixed. Bootloader updated to use switch. The problem was waiting for events in the BDU thread would prevent the IWDG thread to work and trigger a reset. Moved IWDG refreshing to an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
2014-06-15 [Code] Bootloader improvements and fixes.
2014-06-16 [GUI] Adding Firmware XML file generation.
2014-06-16 [Code/GUI] Minor fixes.
2014-06-16 [Code] Add some code for knock ADC handling.
2014-06-17 [Code] Fixed ADC clocks.
2014-06-18 [Code] Minor changes. (cleaning)
2014-06-18 [Code] Adding CAN Bus thread.
2014-06-19 [Code] Updated/Fixed DSP library.
2014-06-19 [Code] Updating Makefiles to use CMSIS CM4 includes instead of Chibi's
2014-06-19 [Code] Increased sensors buffer.
2014-06-20 [Code] Adding eeprom emulation functions.
2014-06-20 [Code] Minor fix.
2014-06-21 [Code] Frequency capture working. Updated board script.
2014-06-22 [GUI] Fixed linux version (PID/VIP were swapped)
2014-06-22 [GUI] Adding basic info for CBR1000RR.
2014-06-22 [Code] Working on DAC driver improvements.
2014-06-23 Updated git submodules URLs.
2014-06-23 [Code] Moving drivers to submodule.
2014-06-23 [Code] Updated DAC driver.
2014-06-23 [Code] DAC driver update.
2014-06-23 [Code] Updating DAC related code and other minor things.
2014-06-23 [Code] Updating mx2board.py and board file for uart2.
2014-06-24 [Code] Updating ChibiOS-RT.
2014-06-24 [Code/GUI] Adding CPU load monitoring.
2014-06-25 [GUI] Updating translation.
2014-06-25 [Code/GUI] Monitoring improvements.
2014-06-25 [Code] Working on monitoring.
2014-06-25 [Code] Monitoring fixes.
2014-06-26 [Code] Monitoring improvements.
2014-06-26 [Code] Fixed serial.
2014-06-27 [Code] Adding echo check to serial thread.
2014-06-27 [Code] Updating drivers submodule.
2014-06-27 [Code] Changed serial thread leds.
2014-06-29 [Board Rev B] USB connector renamed.
2014-07-07 [Board Rev B] Adding voltage reference for VDDA.
2014-08-01 [Board Rev B] Adding an EEPROM
2014-08-04 [Board] Layout improvements
2014-08-15 Adding Knock spectrum widget.
2014-08-17 [Code] Fixed max knock voltage.
2014-08-21 [Code/GUI] Fixed knock signal scale.
2014-08-21 [GUI] Updated translations
2014-08-22 [Code/GUI] Adding median filter Optimizing ADC samples.
2014-08-23 [Code] Minor changes.
2014-10-20 Updated Chibios-RT to V3.0
2014-10-20 Missing vector address
2014-10-20 Various fixes
2014-10-20 Updated drivers
2014-10-21 Fixed ADC
2014-10-21 Various fixes.
2014-10-22 Adding IPC mechanism.
2014-10-22 [code] Re-enabled CCM RAM. (linker scripts)
2014-10-24 [Code] Adding LTO to dsp lib's CFLAGS
2014-11-01 [GUI] XML file saving/loading implemented
2014-11-01 [GUI] Minor improvements
2014-11-01 [GUI] Adding AFR Input type select
2014-11-05 [GUI/Code] Rewrote DSP functions, switched to float; Updated DSP library
2014-11-05 [Code] Updated DAC code
2014-11-07 [GUI] Improvements on tables, working header editor, saving and loading modified header values
2014-11-09 [GUI] real time cell tracking implemented, [Code] Reworked median filter code
2014-11-10 [GUI] Working on context menus
2014-11-10 [Code] Adding Hann window for the FFT
2014-11-11 [Code] Working on knock detection
2014-11-12 [GUI] Adding tear-off tabs
2014-11-13 [GUI] Adding cell live update for AFR and Knock
2014-11-13 [Board A] Fixed resistor values
2014-11-14 [Code] Now using CCM for ISRs and time critical threads
2014-11-15 [Code] Linker script changes (CCM)
2014-11-15 [GUI] Fixed detached tabs that would lose their icons. Updated translation.
2014-11-20 [Code] Adding AFR calculation function and settings struct
2014-11-27 [Code] Adding more commands, changed checksum byte position
2014-11-27 [GUI] Adding more commands (cell clearing), adding logs widget
2014-11-28 [GUI] Adding headers write functions
2015-01-16 [GUI] Fixes for linux (Qt5, GCC)
2015-01-16 [Code] Adding tables
2015-01-18 [Code] Adding K-line DTR handling
2015-01-19 [Code] Adding K-line init to SDU thread.
2015-01-19 [Code] Disable flash latency hack
2015-01-19 [GUI] Adding serial port monitoring
2015-01-24 [Code] Testing K-line init
2015-04-07 Updating Chibios.
2015-08-18 [code] Adding 5 baud init.
2015-08-18 [code] Adding init delay
2015-08-20 [code] Missing serial defines
2015-08-20 [code] Updating contrib repo
2015-08-22 [GUI] Updated QtUsb and code accordingly
2015-08-22 Cleaned sleep calls
2015-08-24 Updating contrib submodule
2015-08-24 Updating Chibios submodule
2015-09-06 [Board] Working on Rev B
2015-09-09 [code] Updating chibios.
2015-09-09 [code] Moving vector table to CCM.
2015-09-10 [code] Fixes
2015-09-10 [Code] Fixed init
2015-09-11 [code] Reverting to GCC 4.8.4
2015-10-17 [Board] working on rev B (full rework)
2015-11-16 [Board] working on rev B (routing/schema)
2015-12-18 git ignore file
2015-12-18 Adding Qt creator project for stm32 code
2015-12-19 [code/GUI] winusb troubleshooting
2015-12-19 QtUSB version update
2015-12-21 [Board] working on rev B (routing/cleaning)
2016-01-18 [Code] Made changes to work with rev B board (uses different pins/peripherals)
2016-01-19 [Code] Updating mx2board to take additional parameters into consideration. (GPIO speed, different config on earch port, etc)
2016-01-20 [code] Fixed mx2board defines generation (wrong pad number)
2016-01-20 [code] Adding timer info to defines generator.
2016-01-20 [Code] Updating app (using new defines)
2016-01-27 Fixing bootloader to work with latest Chibios (16.1)
2016-01-30 [Code] Updates/Fixes for ChibiOS 16.1
2016-01-31 [Code] Fixed vectors table
2016-02-01 [code] Fixed App for Chibi 16.1
2016-02-01 [code] Some cleaning.
2016-02-02 [Code] Updated USB Config
2016-02-03 [Code] Updating monitoring
2016-02-03 [Code/GUI] Implemented new monitoring.
2016-02-03 [GUI/Code] Adding types.
2016-02-04 [Code/GUI] Fixed/Tested dynamic thread monitoring
2016-02-04 [Code] Updated eeprom storage code.
2016-02-05 Cleaning eeprom code
2016-02-05 Enabling DMA for CRC.
2016-02-07 [Code/GUI] Working on settings
2016-02-08 [Code] Working on storage (hardfaults...)
2016-02-09 [Code] Working on storage (still hardfaults...)
2016-02-11 [Code] Working on storage (save/load settings now OK)
2016-02-12 [Code] Working on storage (Fixed)
2016-02-12 [Code] Moving main stack back to RAM (was CCM)
2016-05-04 Testing setting write function
2016-05-16 Updating settings section
2016-06-22 Moving TPS settings to combo boxes
2016-06-22 Cleaning UI.
2016-06-23 Adding sensors abstraction
2016-06-23 [GUI] Log improvements
2016-06-23 [GUI/Code] Adding code to handle analog AFR input
2016-06-27 [GUI/Code] Adding code to handle versions.
2016-06-27 [GUI] Adding version check on wizard.
2016-06-28 [code] Renamed define for consistency
2016-06-28 [Code] Fixed missing version command
2016-10-11 [code] Making changes for GCC 5. Latest Chibios/RT.
2016-11-20 [Code] Updating CMSIS library for GCC5 compatibility
2016-11-21 [GUI] Changed progress bar text location.
2017-01-09 [Code] First try at WCID (WinUSB)
2017-01-09 [code] Adding double nul termination to guid string
2017-01-21 Fixes for Qt 5.8.0
2017-02-15 Update README.md
    Adding image.
2017-02-16 [GUI] Adding support for input selection.
2017-02-17 [Code] Fixes for descriptor.
2017-02-17 [code] Removing binaries
2017-02-17 [GUI] Updating settings
2017-02-18 [gui/code] Various minor fixes
2017-02-19 [code] Finally got WCID working with IAD.
2017-02-19 Removing drivers since we don't need them anymore.
2017-02-20 [code] Adding version check/update on boot, cleaned includes.
2017-02-20 [code] Fixed version eeprom function [GUI] Optimised version functions
2017-02-21 [code/GUI] Getting embedded fw version from chconf.h
2017-02-22 [GUI] Fixed compile errors
2017-02-22 [code] Cleaning
2017-02-22 [code] Fixed makefile
2017-02-23 [Code] Working on RPC
2017-02-24 [Code] Working on nanopb.
2017-04-10 [code] Adding OBD emulator support
2017-04-10 [GUI] Adding OBD emulator support
2017-04-16 [Code] Reverting to WINUSB QtUSB, cleaning structs
2017-04-17 [code] Minor changes, cleaning.
2017-04-19 [code] Fixed analog ratios
2017-04-19 [code/GUI] Adding support functions to read table headers
2017-04-20 [code] Fixing settings struct
2017-04-20 [code] Disabling LTO. Adding semihosting code.
2017-04-21 [code] Fixed tables recording and a bunch of other things
2017-04-21 [Code/GUI] Updating version and fixed usb interface (testing)
2017-04-22 [GUI] Removing all the unused/specific stuff (old HRC import/export, fuel/ign/staging tables) to keep app generic.
2017-04-22 [GUI] Updating "about"
2017-04-22 [GUI] Removed unused connections
2017-04-23 [GUI] Fixed tables headers values.
2017-04-23 [GUI] Minor fix
2017-04-24 [code] PVD protection
2017-04-24 [GUI] Fixed cell edit dialog, improved tables model class.
2017-04-24 [GUI] Minor edits.
2017-04-24 [code] Fixed analog AFR calculation.
2017-04-25 [code] Fixed TPS test values
2017-04-25 [code] Fixed test knock value. [GUI] Changed knock table range (for colors)
2017-04-26 [GUI] Version bump.
2017-04-26 [GUI] Fixed RPM progress bar text format
2017-04-27 [code] Updated mx2board script
2017-04-28 [code] small Fixes
2017-04-30 [all] Fixed OBD (CanBus) emulator.
2017-05-02 [ALL] Cleaning, V0.9.0
2017-05-04 [code] Fixed/tested MTS
2017-05-05 [code] Cleaning MTS, Fixed K-LINE
2017-05-05 [code] Disable recording when engine stopped
2017-05-05 [code] adding sensors debug
2017-05-07 [code] Fixed RPM table lookup [GUI] Updated refresh speed to 40hz
2017-05-07 [code] Fixed bootloader compile error.
2017-05-09 [code] More canbus cleaning
2017-05-09 [GUI] Adding version to title.
2017-05-09 [code] OBD fixes
2017-05-11 [code] updating submodules, using mx2board from contrib repo.
2017-05-11 [board/code] Updating board files
2019-01-07 Deleting dsp lib folder
2019-01-07 Replacing dsp lib by submodule
2019-03-06 Added Jenkinsfile
2019-03-06 Jenkins docker images fixed
2019-03-22 Moving to new QtUsb
2019-03-22 USB endpoint type
2019-03-22 Clean submodule
2019-03-22 Updated python script
2019-03-22 Fix for python script
2019-03-22 Qtusb 0.4.0 (#2)
    * Moving to new QtUsb
    * Clean submodule
    * Updated python script
2020-02-24 Fixes for Chibios 19.1.x
2020-02-25 Updated linker files
2020-02-25 Updated bootloader for ChibiOS 19.1.x
2020-02-25 GUI: clang format
2020-02-25 QtUsb submodule URL
2020-02-25 GUI: Pointers check
2020-02-25 Code: Updated binsize
2020-02-25 All: Adding clang format files
2020-02-25 All: Adding LGTM file
2020-02-26 GUI: QtUsb update
2020-02-27 code: usb_config inclusion guard
2020-02-28 GUI: Updater fixes
2020-02-28 GUI: bootloader pointer checks

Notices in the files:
parts and their libraries:
SparkFun-Passives: Licensing: CC v3.0 Share-Alike You are welcome to use this library for commercial purposes.
microbuilder: This work is placed in the public domain, and may be freely used for commercial and non-commercial work with the following conditions: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
